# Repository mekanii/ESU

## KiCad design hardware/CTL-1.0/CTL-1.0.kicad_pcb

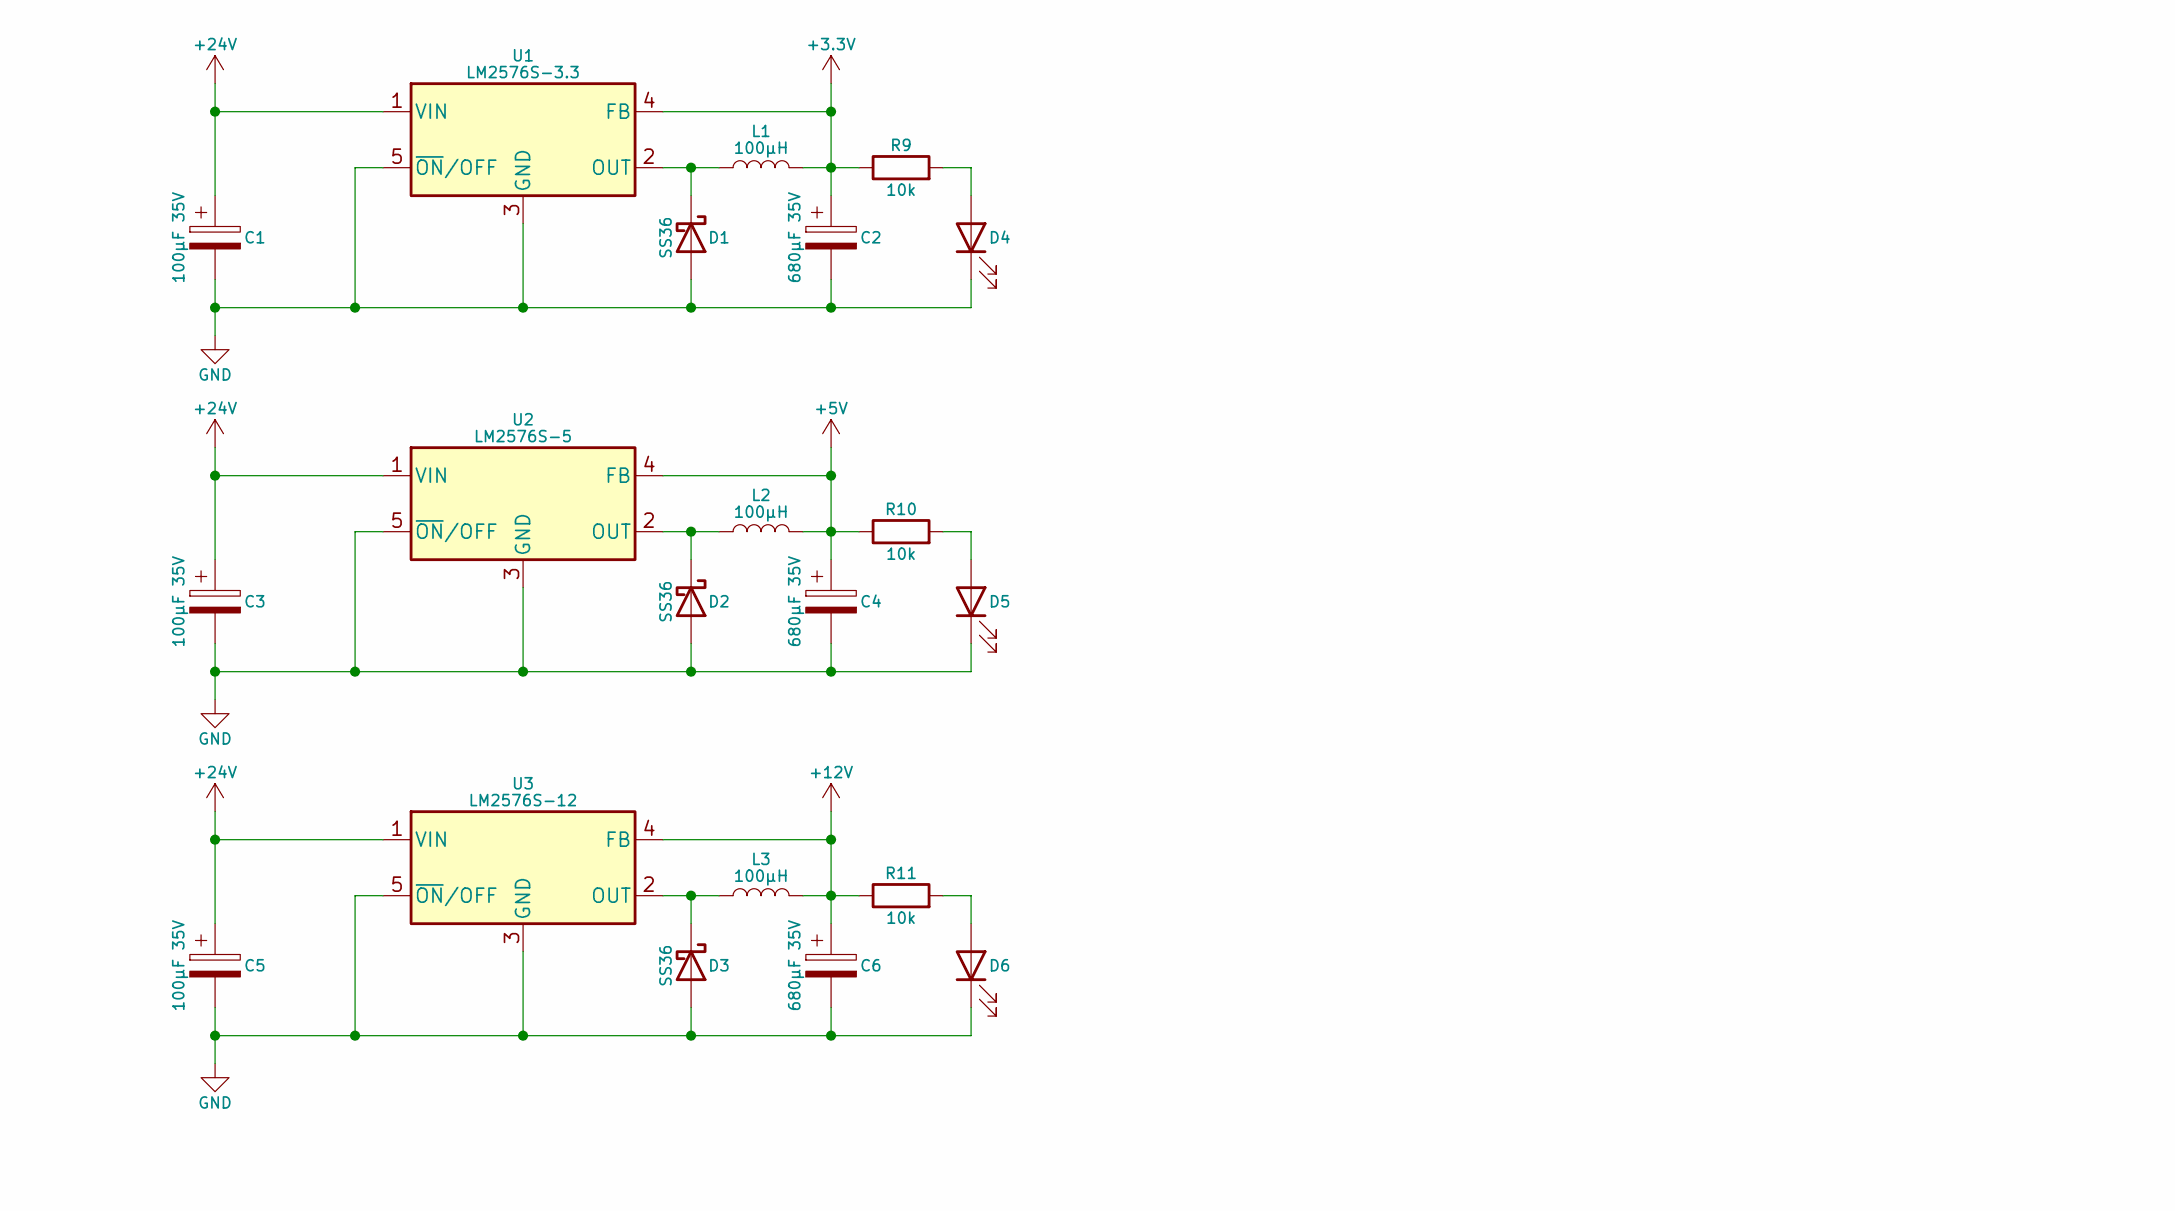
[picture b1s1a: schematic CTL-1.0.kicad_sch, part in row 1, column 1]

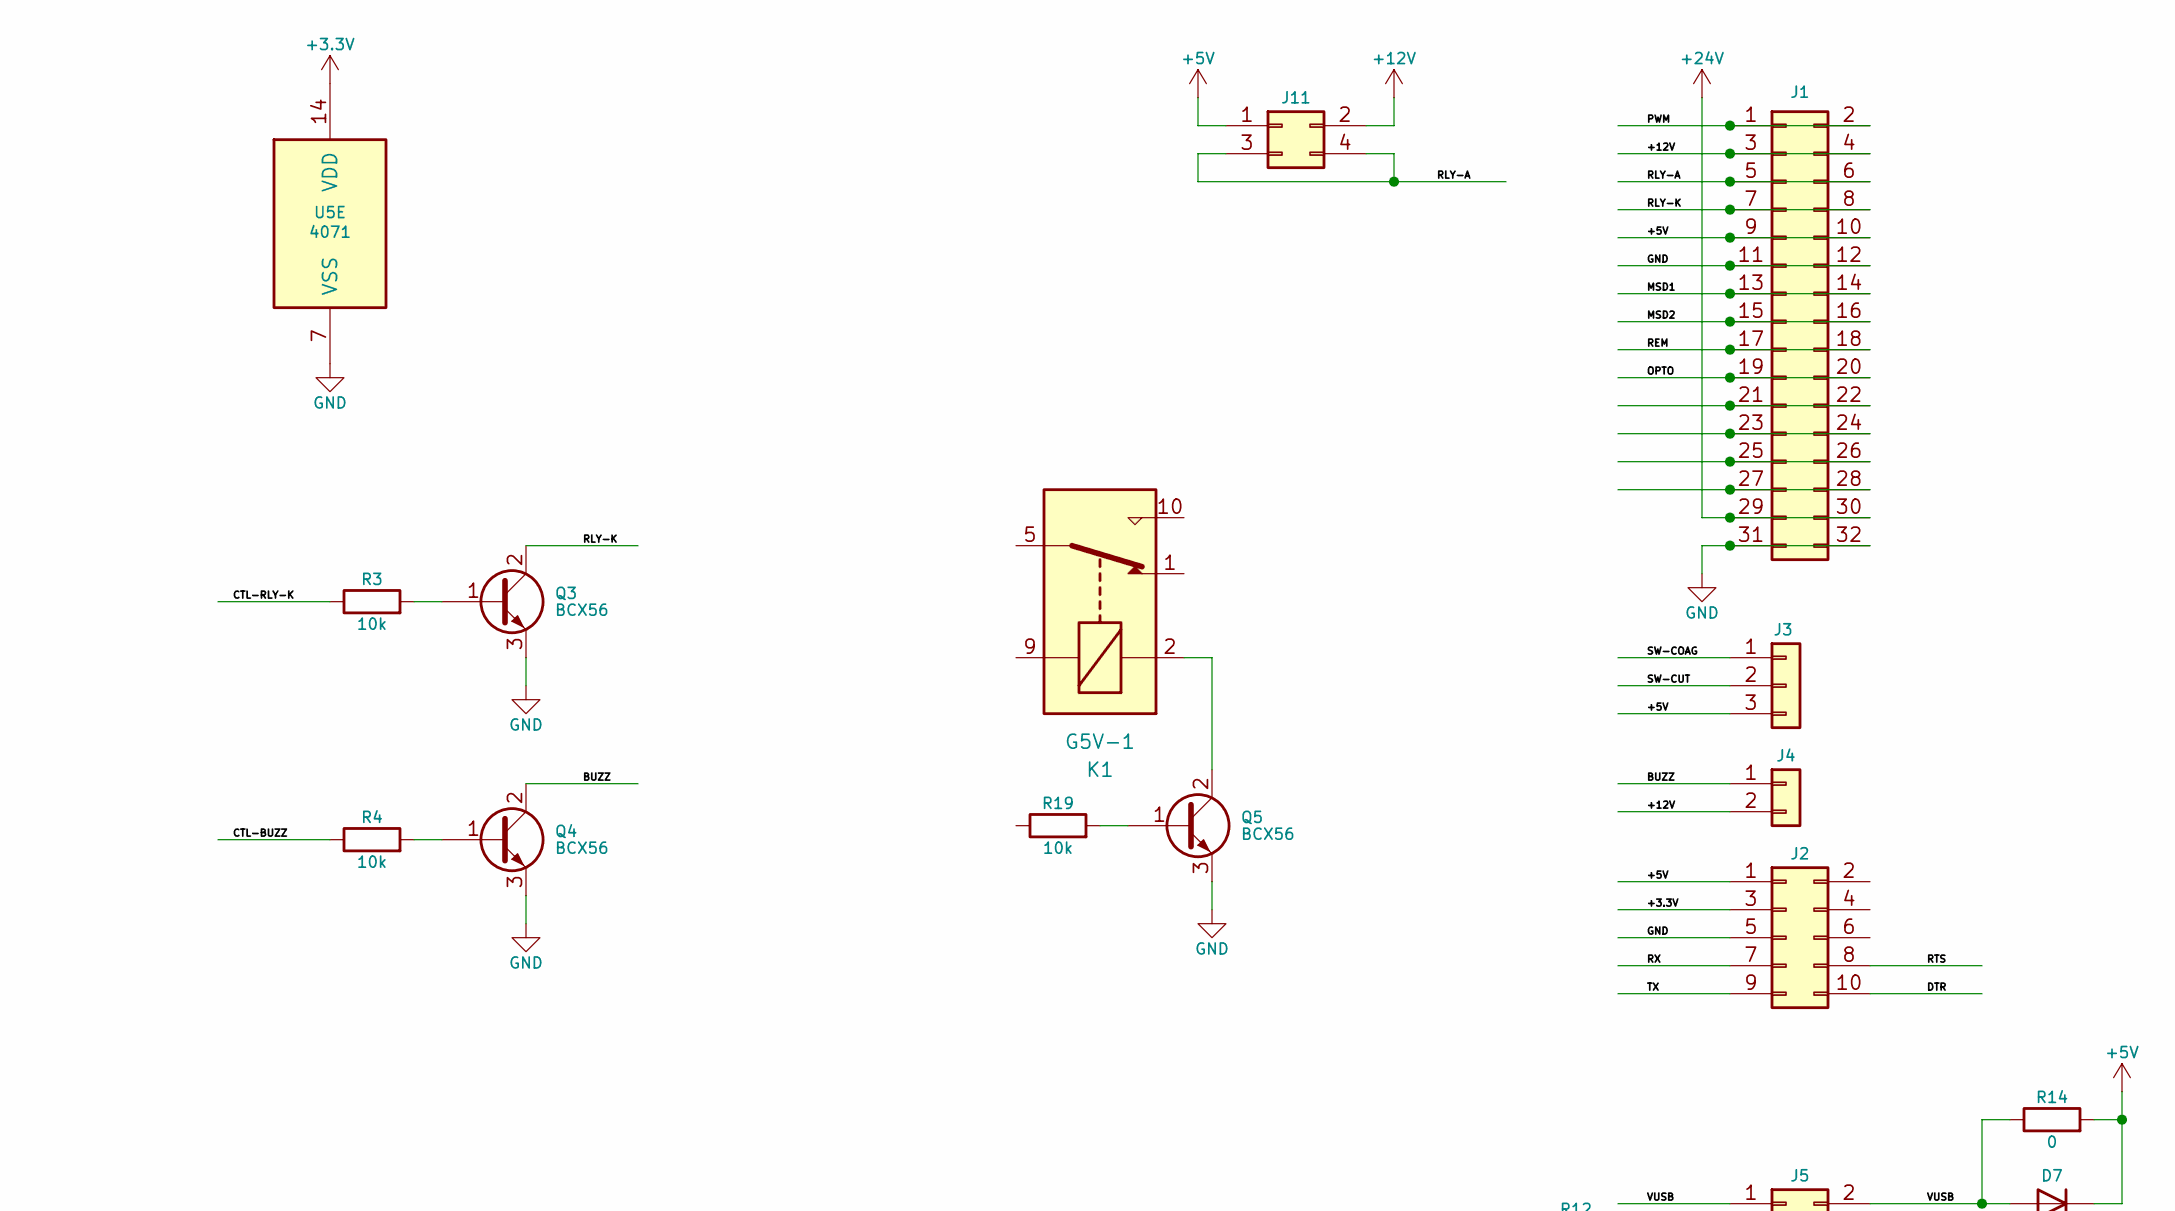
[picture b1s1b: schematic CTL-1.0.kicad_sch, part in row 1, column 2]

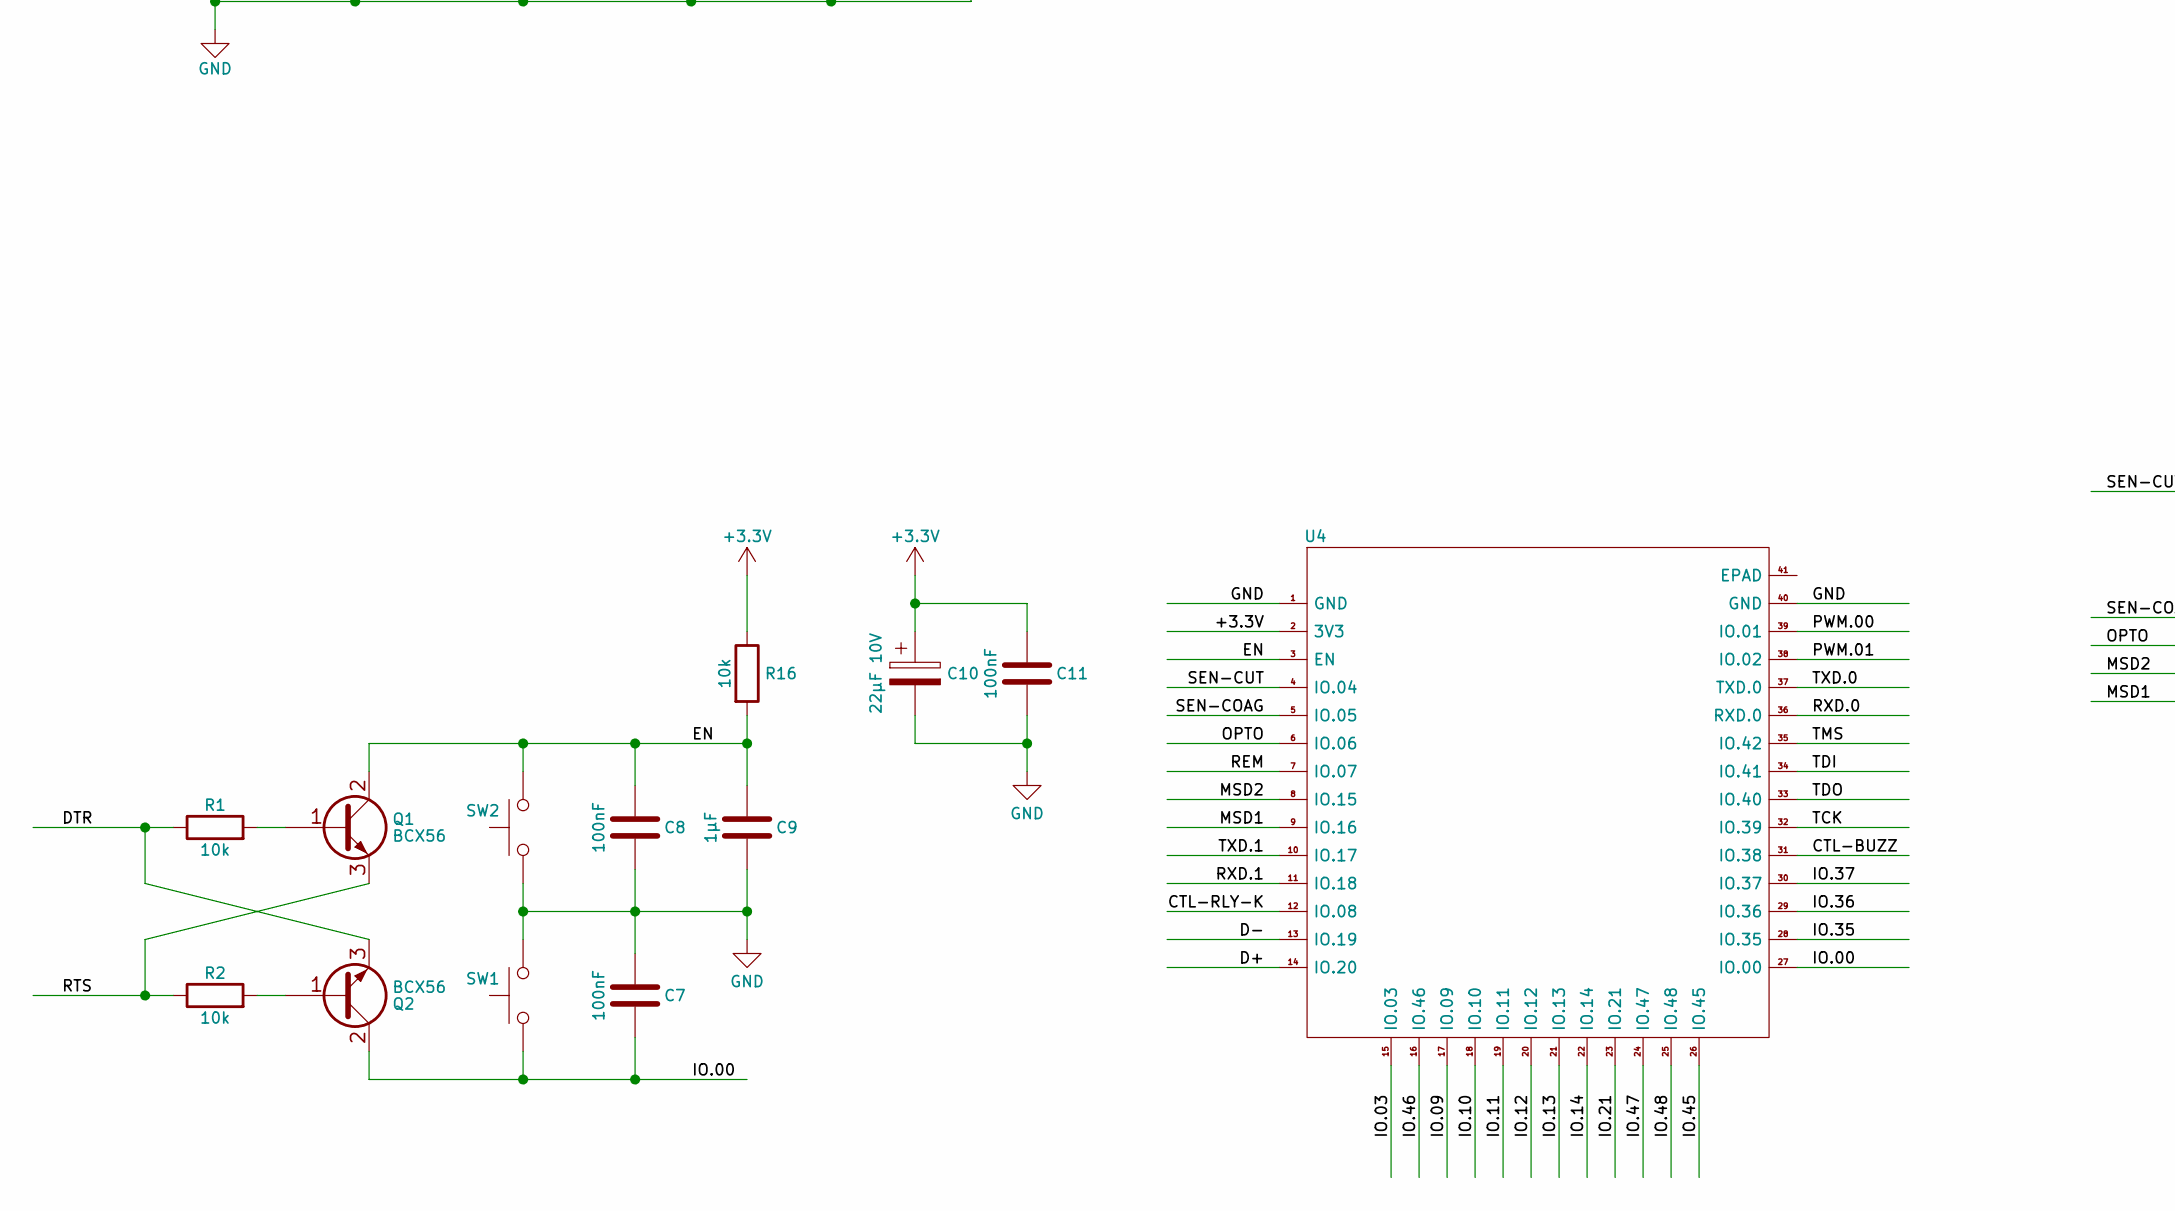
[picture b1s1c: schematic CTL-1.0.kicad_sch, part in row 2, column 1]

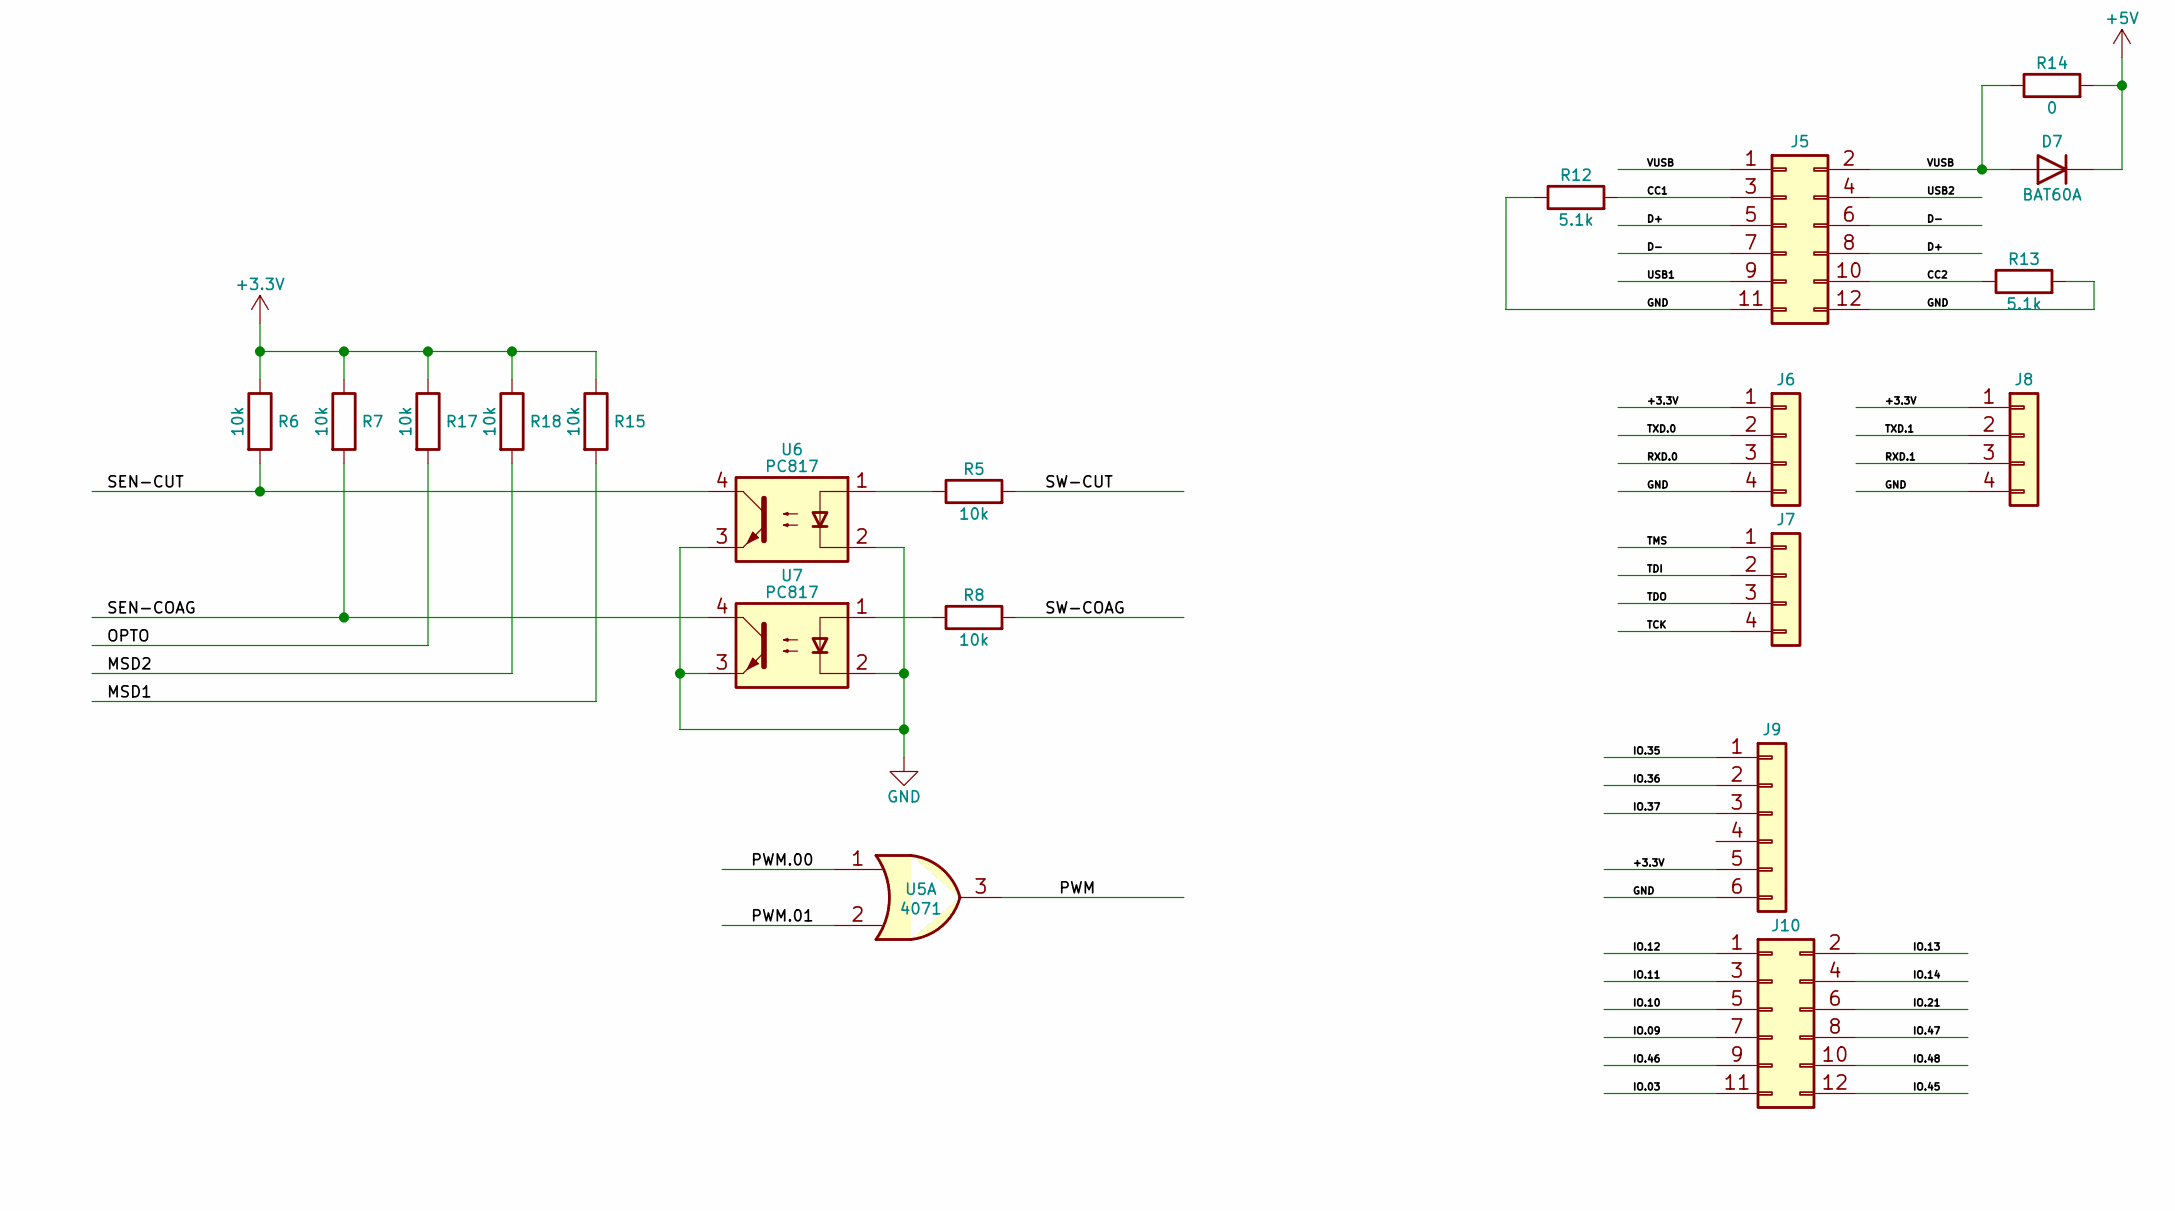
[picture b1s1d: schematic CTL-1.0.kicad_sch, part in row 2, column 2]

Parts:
C1, C3, C5: 100µF 35V; CP_Elec_10x10
C2, C4, C6: 680µF 35V; CP_Elec_10x10
C7, C8, C11: 100nF; C_1206_3216Metric_Pad1.33x1.80mm_HandSolder
C9: 1µF; C_1206_3216Metric_Pad1.33x1.80mm_HandSolder
C10: 22µF 10V; CP_EIA-3528-12_Kemet-T_Pad1.50x2.35mm_HandSolder
D1, D2, D3: SS36; D_SMA
D4, D5, D6: LED; LED_1206_3216Metric_Pad1.42x1.75mm_HandSolder
D7: BAT60A; D_SMB_Handsoldering
J1: Conn_02x16_Top_Bottom; PinHeader_2x16_P2.54mm_Horizontal_NoPins
J2: Conn_02x05_Odd_Even; PinHeader_2x05_P2.54mm_Vertical
J3: Conn_01x03; Molex_KK-396_5273-03A_1x03_P3.96mm_Vertical
J4: Conn_01x02; Molex_KK-396_5273-02A_1x02_P3.96mm_Vertical
J5, J10: Conn_02x06_Odd_Even; PinHeader_2x06_P2.54mm_Vertical
J6, J7, J8: Conn_01x04; PinHeader_1x04_P2.54mm_Vertical
J9: Conn_01x06; PinHeader_1x06_P2.54mm_Vertical
J11: Conn_02x02_Odd_Even; PinHeader_2x02_P2.54mm_Vertical
K1: G5V-1; Relay_SPDT_Omron_G5V-1
L1, L2, L3: 100µH; L_12x12mm_H8mm
Q1, Q2, Q3, Q4, Q5: BCX56; SOT-89-3
R1, R2, R3, R4, R5, R6, R7, R8, R9, R10, R11, R15, R16, R17, R18, R19: 10k; R_1206_3216Metric_Pad1.30x1.75mm_HandSolder
R12, R13: 5.1k; R_1206_3216Metric_Pad1.30x1.75mm_HandSolder
R14: 0; R_1206_3216Metric_Pad1.30x1.75mm_HandSolder
SW1, SW2: SW_Omron_B3FS; SW_SPST_Omron_B3FS-100xP
U1: LM2576S-3.3; TO-263-5_TabPin3
U2: LM2576S-5; TO-263-5_TabPin3
U3: LM2576S-12; TO-263-5_TabPin3
U4: ESP32-S3-WROOM-1U
U5: 4071; DIP-14_W8.89mm_SMDSocket_LongPads
U6, U7: PC817; DIP-4_W7.62mm_Socket

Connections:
+3.3V: C2.1, C10.1, C11.2, J2.3, J6.1, J8.1, J9.5, L1.2, R6.1, R7.1, R9.1, R15.1, R16.1, R17.1, R18.1, U1.4 (FB), U4.2 (3V3), U5.14 (VDD)
+5V: C4.1, D7.1 (K), J1.9, J1.10, J2.1, J3.3, J11.1, L2.2, R10.1, R14.2, U2.4 (FB)
+12V: C6.1, J1.3, J1.4, J4.2, J11.2, L3.2, R11.1, U3.4 (FB)
+24V: C1.1, C3.1, C5.1, J1.29, J1.30, U1.1 (VIN), U2.1 (VIN), U3.1 (VIN)
/BUZZ: J4.1, Q4.2 (C)
/CC1: J5.3, R12.2
/CC2: J5.10, R13.1
/CTL-BUZZ: R4.1, U4.31 (IO.38)
/CTL-RLY-K: R3.1, U4.12 (IO.08)
/D+: J5.5, J5.8, U4.14 (IO.20)
/D-: J5.6, J5.7, U4.13 (IO.19)
/DTR: J2.10, Q2.3 (E), R1.1
/EN: C8.2, C9.2, Q1.2 (C), R16.2, SW2.2, U4.3 (EN)
/IO.00: C7.2, Q2.2 (C), SW1.1, U4.27 (IO.00)
/IO.03: J10.11, U4.15 (IO.03)
/IO.09: J10.7, U4.17 (IO.09)
/IO.10: J10.5, U4.18 (IO.10)
/IO.11: J10.3, U4.19 (IO.11)
/IO.12: J10.1, U4.20 (IO.12)
/IO.13: J10.2, U4.21 (IO.13)
/IO.14: J10.4, U4.22 (IO.14)
/IO.21: J10.6, U4.23 (IO.21)
/IO.35: J9.1, U4.28 (IO.35)
/IO.36: J9.2, U4.29 (IO.36)
/IO.37: J9.3, U4.30 (IO.37)
/IO.45: J10.12, U4.26 (IO.45)
/IO.46: J10.9, U4.16 (IO.46)
/IO.47: J10.8, U4.24 (IO.47)
/IO.48: J10.10, U4.25 (IO.48)
/MSD1: J1.13, J1.14, R15.2, U4.9 (IO.16)
/MSD2: J1.15, J1.16, R18.2, U4.8 (IO.15)
/OPTO: J1.19, J1.20, R17.2, U4.6 (IO.06)
/PWM: J1.1, J1.2, U5.3
/PWM.00: U4.39 (IO.01), U5.1
/PWM.01: U4.38 (IO.02), U5.2
/REM: J1.17, J1.18, U4.7 (IO.07)
/RLY-A: J1.5, J1.6, J11.3, J11.4
/RLY-K: J1.7, J1.8, Q3.2 (C)
/RTS: J2.8, Q1.3 (E), R2.1
/RX: J2.7
/RXD.0: J6.3, U4.36 (RXD.0)
/RXD.1: J8.3, U4.11 (IO.18)
/SEN-COAG: R7.2, U4.5 (IO.05), U7.4
/SEN-CUT: R6.2, U4.4 (IO.04), U6.4
/SW-COAG: J3.1, R8.2
/SW-CUT: J3.2, R5.2
/TCK: J7.4, U4.32 (IO.39)
/TDI: J7.2, U4.34 (IO.41)
/TDO: J7.3, U4.33 (IO.40)
/TMS: J7.1, U4.35 (IO.42)
/TX: J2.9
/TXD.0: J6.2, U4.37 (TXD.0)
/TXD.1: J8.2, U4.10 (IO.17)
/USB1: J5.9
/USB2: J5.4
/VUSB: D7.2 (A), J5.1, J5.2, R14.1
GND: C1.2, C2.2, C3.2, C4.2, C5.2, C6.2, C7.1, C8.1, C9.1, C10.2, C11.1, D1.2 (A), D2.2 (A), D3.2 (A), D4.1 (K), D5.1 (K), D6.1 (K), J1.11, J1.12, J1.31, J1.32, J2.5, J5.11, J5.12, J6.4, J8.4, J9.6, Q3.3 (E), Q4.3 (E), Q5.3 (E), R12.1, R13.2, SW1.2, SW2.1, U1.3 (GND), U1.5 (~ON/OFF), U2.3 (GND), U2.5 (~ON/OFF), U3.3 (GND), U3.5 (~ON/OFF), U4.1 (GND), U4.40 (GND), U5.7 (VSS), U6.2, U6.3, U7.2, U7.3
unnamed: D1.1 (K), L1.1, U1.2 (OUT)
unnamed: D2.1 (K), L2.1, U2.2 (OUT)
unnamed: D3.1 (K), L3.1, U3.2 (OUT)
unnamed: D4.2 (A), R9.2
unnamed: D5.2 (A), R10.2
unnamed: D6.2 (A), R11.2
unnamed: J1.21, J1.22
unnamed: J1.23, J1.24
unnamed: J1.25, J1.26
unnamed: J1.27, J1.28
unnamed: K1.5, K1.6
unnamed: Q1.1 (B), R1.2
unnamed: Q2.1 (B), R2.2
unnamed: Q3.1 (B), R3.2
unnamed: Q4.1 (B), R4.2
unnamed: Q5.1 (B), R19.2
unnamed: K1.2, Q5.2 (C)
unnamed: R5.1, U6.1
unnamed: R8.1, U7.1

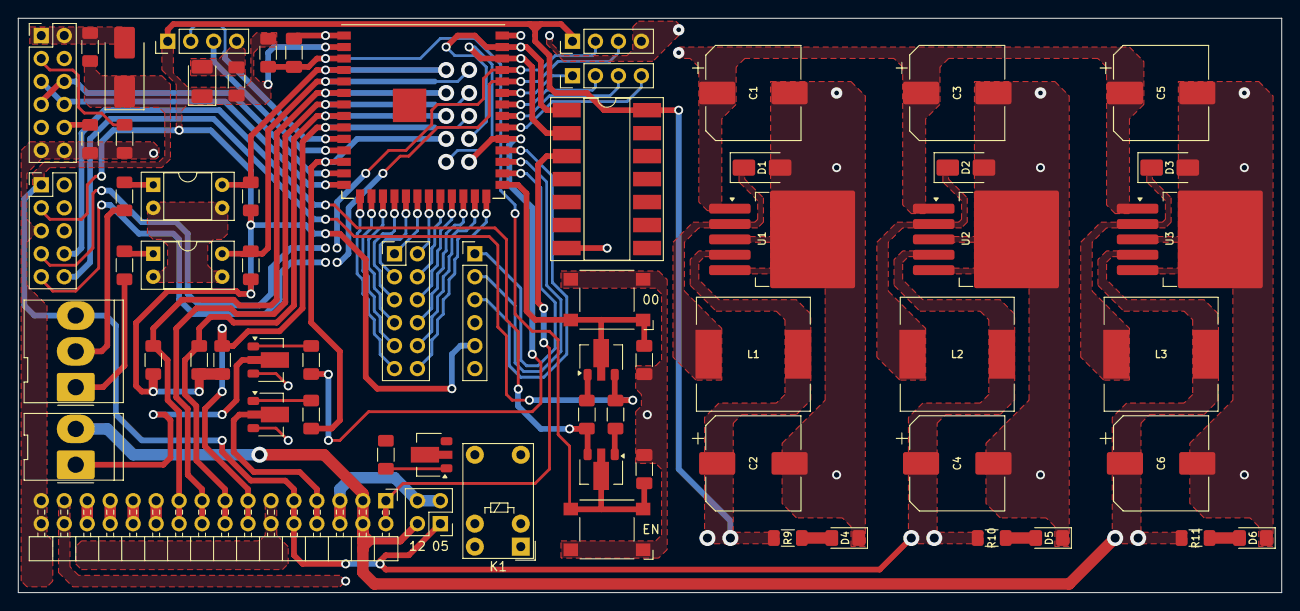
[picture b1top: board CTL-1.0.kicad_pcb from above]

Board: 2 copper layers, 139.7 x 63.5 mm, 66 parts (0 on the bottom side), 72 nets.

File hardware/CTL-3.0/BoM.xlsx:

# | Sourced | Placed | References | Value | Footprint | Quantity
1 | ✅ |  | R1, R2, R3, R4, R5, R6, R7, R8, R9, R10, R11, R15, R16, R17, R18, R19 | 10k | R_1206_3216Metric_Pad1.30x1.75mm_HandSolder | 16 | https://www.tokopedia.com/lisuinstrument/10k-1206-1-250mw-20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
2 | ✅ |  | R12, R13 | 5.1k | R_1206_3216Metric_Pad1.30x1.75mm_HandSolder | 2 | https://www.tokopedia.com/lisuinstrument/5-1k-1206-1-250mw-2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
3 | ✅ |  | R14 | 0 | R_1206_3216Metric_Pad1.30x1.75mm_HandSolder | 1 | https://www.tokopedia.com/lisuinstrument/0-1206-5-smd-thick-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
4 | ✅ |  | C1, C3, C5 | 100µF 35V | CP_Elec_10x10 | 3 | https://www.tokopedia.com/jayenk/solid-kapasitor-capasitor-e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
5 | ✅ |  | C2, C4, C6 | 680µF 35V | CP_Elec_10x10 | 3 | https://www.tokopedia.com/jayenk/solid-kapasitor-capasitor-e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
6 | ✅ |  | C7, C8, C11 | 100nF | C_1206_3216Metric_Pad1.33x1.80mm_HandSolder | 3 | https://www.tokopedia.com/lisuinstrument/100nf-50v-x7r-10-12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
7 | ✅ |  | C9 | 1µF | C_1206_3216Metric_Pad1.33x1.80mm_HandSolder | 1 | https://www.tokopedia.com/lisuinstrument/1uf-10-50v-x7r-1206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
8 | ✅ |  | C10 | 22µF 10V | CP_EIA-3528-12_Kemet-T_Pad1.50x2.35mm_HandSolder | 1 | https://www.tokopedia.com/putraniagabdg/tantalum-smd-22uf-10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
9 | ✅ |  | L1, L2, L3 | 100µH | L_12x12mm_H8mm | 3 | https://www.tokopedia.com/elantech/induktor-smd-100uh-1-7a-1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
10 | ✅ |  | D1, D2, D3 | SS36 | D_SMA | 3 | https://www.tokopedia.com/lisuinstrument/ss36a-60v-3a-schott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
11 | ✅ |  | D4, D5, D6 | LED | LED_1206_3216Metric_Pad1.42x1.75mm_HandSolder | 3 | https://www.tokopedia.com/lisuinstrument/1206-smd-led-smt-ul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
12 | ✅ |  | D7 | BAT60A | D_SMB_Handsoldering | 1 | https://www.tokopedia.com/lisuinstrument/ss36b-60v-3a-schott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
13 | ✅ |  | U6, U7 | PC817 | DIP-4_W7.62mm_Socket | 2 | https://www.tokopedia.com/putraniagabdg/pc817-optocoupler-pc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
14 | ✅ |  | U1 | LM2576S-3.3 | TO-263-5_TabPin3 | 1 | https://www.tokopedia.com/starelektro-1/lm2576s-lm2576hvs-ad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
15 | ✅ |  | U2 | LM2576S-5 | TO-263-5_TabPin3 | 1 | https://www.tokopedia.com/starelektro-1/lm2576s-lm2576hvs-ad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
16 | ✅ |  | U3 | LM2576S-12 | TO-263-5_TabPin3 | 1 | https://www.tokopedia.com/starelektro-1/lm2576s-lm2576hvs-ad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
17 | ✅ |  | U4 | ESP32-S3-WROOM-1U | ESP32-S3-WROOM-1U | 1 | https://www.tokopedia.com/the-diy-store/esp32-s3-wroom-esp32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
18 | ✅ |  | U5 | 4071 | DIP-14_W8.89mm_SMDSocket_LongPads | 1 | https://www.tokopedia.com/smgjayatronik/cd4071bcm-cd4071-smd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
19 | ✅ |  | SW1, SW2 | SW_Omron_B3FS | SW_SPST_Omron_B3FS-100xP | 2 | https://www.tokopedia.com/putraniagabdg/push-on-4p-mini-pcb-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
20 | ✅ |  | Q1, Q2, Q3, Q4, Q5 | BCX56 | SOT-89-3 | 5 | https://www.tokopedia.com/lisuinstrument/bcx56-npn-80v-1a-50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
21 | ✅ |  | TP1, TP2, TP3 | TestPoint | TestPoint_Bridge_Pitch2.54mm_Drill1.0mm | 3
22 | ✅ |  | K1 | G5V-1 | Relay_SPDT_Omron_G5V-1 | 1 | https://www.tokopedia.com/celectro/relay-g5v-1-5vdc
23 | ✅ |  | J7, J8 | Conn_01x04 | PinHeader_1x04_P2.54mm_Vertical | 2
24 | ✅ |  | J1 | Conn_02x16_Top_Bottom | PinHeader_2x16_P2.54mm_Horizontal_NoPins | 1 | https://www.tokopedia.com/putraniagabdg/header-male-siku-2x4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
25 | ✅ |  | J3 | Conn_01x03 | Molex_KK-396_5273-03A_1x03_P3.96mm_Vertical | 1 | https://www.tokopedia.com/putraniagabdg/1-set-konektor-heade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
26 | ✅ |  | J4 | Conn_01x02 | Molex_KK-396_5273-02A_1x02_P3.96mm_Vertical | 1 | https://www.tokopedia.com/putraniagabdg/1-set-konektor-heade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
27 | ✅ |  | J5 | Conn_02x06_Odd_Even | PinHeader_2x06_P2.54mm_Vertical | 1 | https://www.tokopedia.com/putraniagabdg/header-male-baris-2x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
28 | ✅ |  | J6 | Conn_01x04 | PinHeader_1x06_P2.54mm_Vertical | 1 | https://www.tokopedia.com/putraniagabdg/header-male-baris-1x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
